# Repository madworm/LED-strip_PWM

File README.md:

LED-strip_PWM
=============

LAYOUT FILES: Tiny LED-strip PWM controller. 2 potentiometers are used as user-input.

You will find code for this project in [this](https://github.com/madworm/ATtiny_projects/tree/master/13/LED-strip_PWM) repository.

---

Before having PC-boards made, please make sure you know about your manufacturer's peculiarities!
Especially drill-sizes and their tolerances may vary too much and give you trouble.

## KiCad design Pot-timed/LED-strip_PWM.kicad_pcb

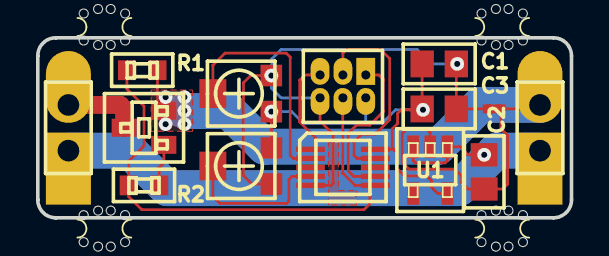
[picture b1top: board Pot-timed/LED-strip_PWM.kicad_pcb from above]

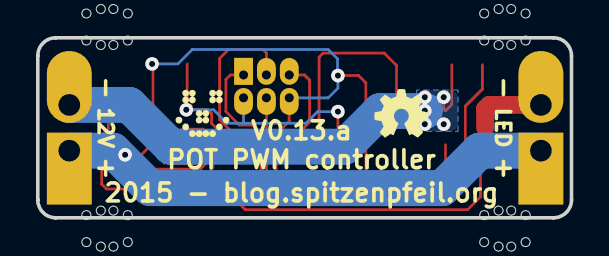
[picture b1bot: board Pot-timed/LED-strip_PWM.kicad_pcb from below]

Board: 2 copper layers, 29.7 x 10.0 mm, 20 parts (2 on the bottom side), 12 nets.

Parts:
C1, C2: 100nF; MADW__C0805
C3: 4.7µF; MADW__C0805
G1: OSHW-logo_silkscreen_3mm
G2: LED_smile_silkscreen_3mm
IC1: MADW__ATTINY13-MM; MADW__MLF10
JP1: ISP; MADW__PIN_ARRAY_3x2_1.27mm
NJ1: NET-JOIN; MADW__SMD-net-noin-0.5mm
P1, P2: CONN_2; MADW__SIL-2
R1: 100k; MADW__R0603_2
R2: 150R; MADW__R0603_2
RV1, RV2: 50k; MADW__TC33X-POT
T1: AO3400; MADW__SOT23
U1: AP2204K-3.3TRG1; MADW__SOT23-5
mouse-bite-1mm, mouse-bite-1mm#2, mouse-bite-1mm#3, mouse-bite-1mm#4: VAL**; mouse-bite-1mm-slot

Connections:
/MISO: IC1.7, JP1.1
/MOSI: IC1.6, JP1.4, R1.2, R2.1
/POT1: IC1.2, RV1.2
/POT2: IC1.4, RV2.2
/RESET: IC1.1, JP1.5
/SCK: IC1.9, JP1.3
/Vin: C2.1, P1.1, P2.1, U1.1, U1.3
/drain: P2.2, T1.3
GND: C1.2, C3.2, IC1.5, JP1.6, NJ1.1, RV1.3, RV2.1
GNDPWR: C2.2, NJ1.2, P1.2, R1.1, T1.2, U1.2
unnamed: R2.2, T1.1
VCC: C1.1, C3.1, IC1.10, JP1.2, RV1.1, RV2.3, U1.5

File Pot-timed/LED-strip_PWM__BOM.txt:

Bill of materials:
------------------

C1, C2		100nF, 50V			0805
C3		4.7uF, 10V			0805
IC1		ATTINY13-MM			DFN10
R1		100k				0603
R2		150R				0603
RV1, RV2	Bourns, TC33X, ~10k
T1		AO3400 / IRLML6344TRPBF		SOT23
U1		AP2204K-3.3TRG1 [TS5205CX533]	SOT23-5

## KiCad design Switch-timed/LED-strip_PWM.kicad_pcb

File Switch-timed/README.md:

LED-strip_PWM_IR
================

LAYOUT FILES: Small high-current PWM controller with IR receiver (ATtiny85 based). 

---

Before having PC-boards made, please make sure you know about your manufacturer's peculiarities!
Especially drill-sizes and their tolerances may vary too much and give you trouble.

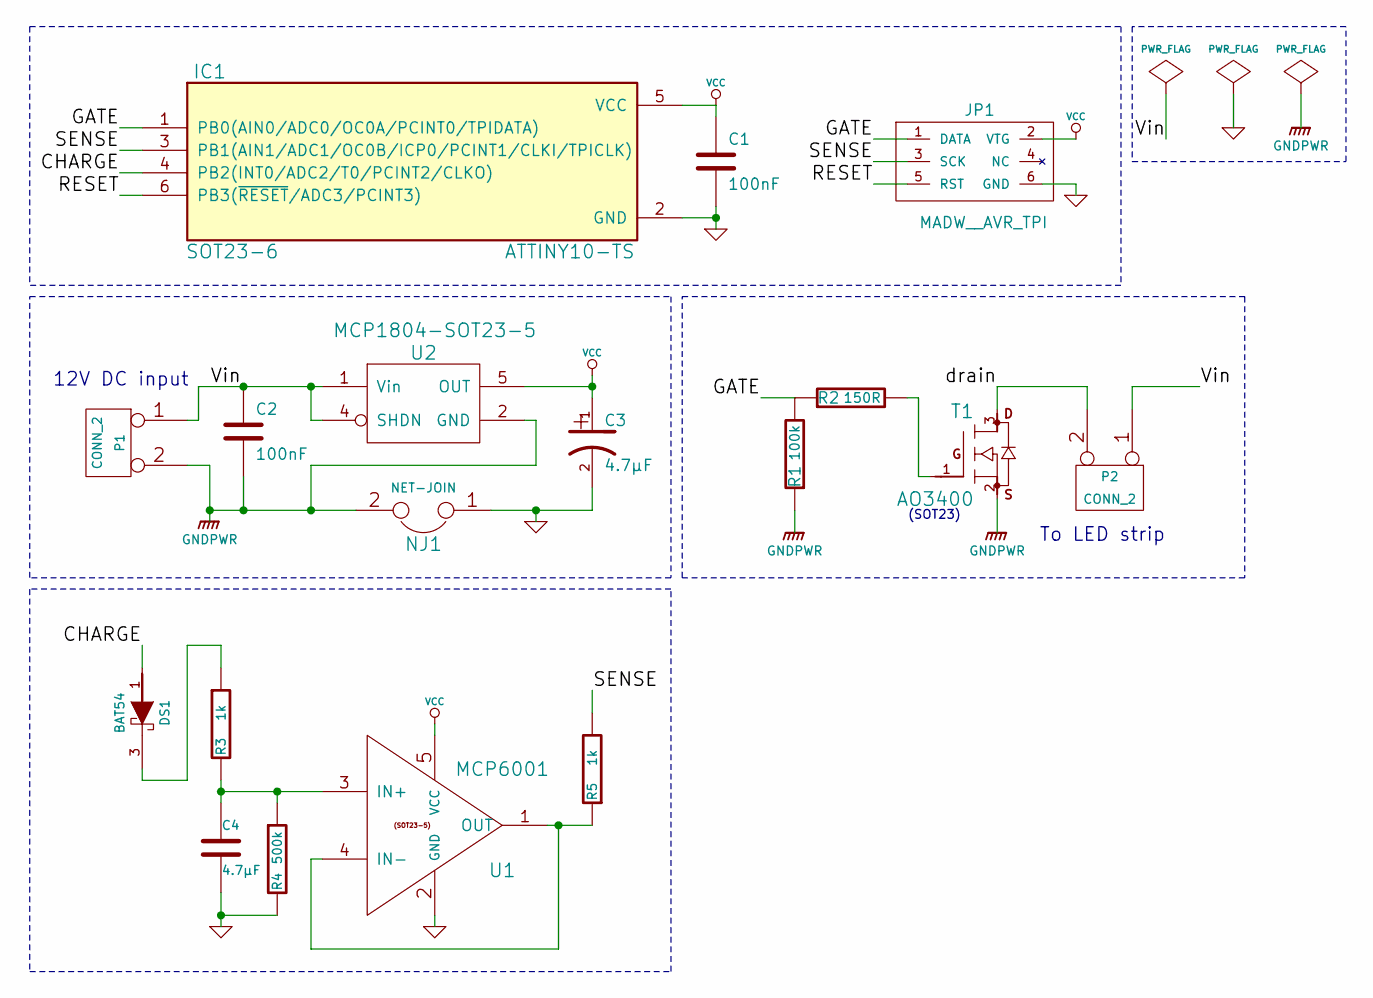
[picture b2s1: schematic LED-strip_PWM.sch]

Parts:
C1, C2: 100nF
C3: 4.7µF
C4: 4.7µF
DS1: BAT54
IC1: ATTINY10-TS; SOT23-6
JP1: MADW__AVR_TPI
NJ1: NET-JOIN
P1, P2: CONN_2
R1: 100k
R2: 150R
R3: 1k
R4: 500k
R5: 1k
T1: AO3400
U1: MCP6001
U2: MCP1804-SOT23-5

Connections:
/CHARGE: DS1.1 (A), IC1.4 (PB2(INT0/ADC2/T0/PCINT2/CLKO))
/GATE: IC1.1 (PB0(AIN0/ADC0/OC0A/PCINT0/TPIDATA)), JP1.1 (DATA), R1.2, R2.1
/RESET: IC1.6 (PB3(~RESET~/ADC3/PCINT3)), JP1.5 (RST)
/SENSE: IC1.3 (PB1(AIN1/ADC1/OC0B/ICP0/PCINT1/CLKI/TPI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), JP1.3 (SCK), R5.2
/Vin: C2.1, P1.1, P2.1, U2.1 (Vin), U2.4 (SHDN)
/drain: P2.2 (PM), T1.3 (D)
GND: C1.2, C3.2, C4.2, IC1.2 (GND), JP1.6 (GND), NJ1.1, R4.2, U1.2 (GND)
GNDPWR: C2.2, NJ1.2, P1.2 (PM), R1.1, T1.2 (S), U2.2 (GND)
unnamed: DS1.3 (C), R3.1
unnamed: R5.1, U1.1 (OUT), U1.4 (IN-)
unnamed: C4.1, R3.2, R4.1, U1.3 (IN+)
unnamed: R2.2, T1.1 (G)
VCC: C1.1, C3.1, IC1.5 (VCC), JP1.2 (VTG), U1.5 (VCC), U2.5 (OUT)

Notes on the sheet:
To LED strip
12V DC input
(SOT23)

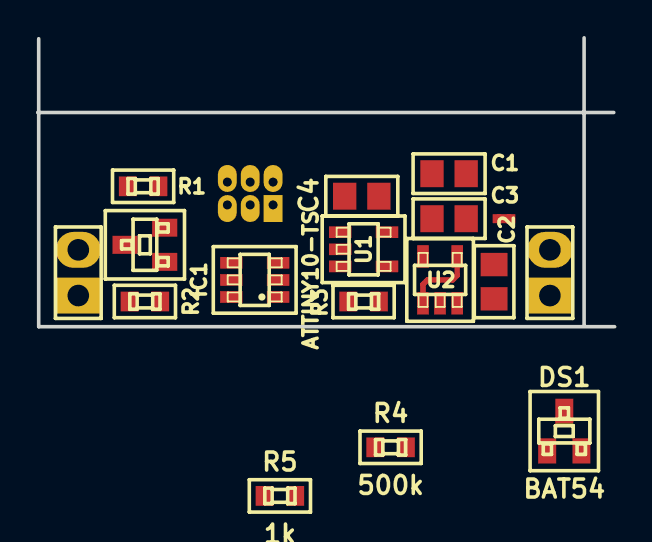
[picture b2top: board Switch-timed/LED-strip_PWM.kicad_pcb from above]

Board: 2 copper layers, 32.0 x 16.0 mm, 18 parts (1 on the bottom side), 13 nets.

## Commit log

2013-05-25 Pot-timed: Attiny13 MLF10 (Unobtanium) --> MLF20.
2013-05-25 Switch-timed: switched Attiny13 footprint.
2013-05-25 Pot-timed: Found Attiny13 MLF10 at digikey...
2013-05-25 Updated 'README.md'.
2013-05-25 Pot-timed: Added an improvised center-pad to the MLF10 footprint.
2013-05-25 Pot-timed: All 6-mil traces (except high-current ones).
2013-05-25 Switch-timed: forgot RC-timer resistor + added BAT54.
2013-05-25 Pot-timed: Playing with panelization again. TEDIOUS...
2013-05-26 Pot-timed: 12x3 panel done.
2013-05-26 Pot-timed: 12x3 panel tweaks.
2013-05-26 Paste layers were missing... again.
2013-05-27 Pot-timed: Reworking the panel.
    KiCad really ought to know about the concept of 'linked clones' for boards.
    Modify the 'parent' and all clones get updated automatically.
2013-05-27 Pot-timed: Forgot logos. Panel now 100% V-groove.
2013-05-28 Pot-timed: Tweaked the panel (paste layer for stencil).
2013-05-28 Pot-timed: Layout tweaks (single board).
2013-05-28 Pot-timed: Panel partially updated.
2013-06-07 Changed to custom attiny13 schematic symbol + footprint.
2013-06-13 Pot-timed (single board): rounded corners.
2013-06-16 Pot-timed (single board): switched to ATtiny10 SOT23-6.
2013-06-16 Switch-timed: switched to ATtiny10 SOT23-6.
2013-06-18 Revert "Switch-timed: switched to ATtiny10 SOT23-6."
    This reverts commit 7426c306dc58e77c9809db77e26f6b62b76c1d9c.
    C + ATtiny10 not supported by avr-gcc
2013-06-18 Revert "Pot-timed (single board): switched to ATtiny10 SOT23-6."
    This reverts commit c61ef78eb5273ce0300997b1b0118eed30148325.
    C + ATtiny10 not supported by avr-gcc
2013-06-25 Pot-timed (single board): Smaller drills for pogo-pin ISP connector.
2013-06-28 Enlarged the center-pad of MLF10 to access it with the iron.
2013-07-01 Pot-timed (single board): tweaks + MLF10: extended all pads.
2013-07-08 Pot-timed (single board): removed B_Mask from pogo-pin footprint.
2013-07-15 Pot-timed (panel): resized to 10cm x 10cm.
2013-07-15 Pot-timed (panel): tweaked to 9.9cm x 10cm.
2013-07-17 Pot-timed (panel): filled with boards.
2013-07-17 Pot-timed (s.b.): added alternative MOSFET to schematic + Rev. update.
2013-08-09 Pot-timed (s.b.): added info helpful for panelization.
2013-08-09 Pot-timed (panels): Created a routed panel.
2013-08-09 Upgraded 'make_all-pngs.sh'
2013-08-09 Pot-timed (panels): Created gerber files for the routed panel.
2013-08-11 Changed fiducial size on all panels.
2013-08-16 Updatd 'README.md'.
2013-09-13 Pot-timed: added 'measurements.txt' with some Rds / power-loss data.
2014-08-23 Pot-timed: added simple BOM file.
2014-12-20 Removed the 'Switch-timed' stuff. Never going to finish it anyway.
2015-01-29 Created 'Docs' folder.
2015-04-02 Replaced MCP1804 with AP2204K-3.3TRG1 [TS5205CX533].
2015-04-02 Removed v-cut panel files & corrected minor routing path issue.
2017-01-21 Fixed broken PDF of schematic.
